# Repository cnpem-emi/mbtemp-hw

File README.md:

MBTemp
=====

MBTemp is an electronic board to acquire temperature in eight independent channels. It has been developed by the Control Group of Brazilian Synchrotron Light Laboratory (LNLS).

Example
-------

An example of use is present in the well documented file `exemplo-mbtemp.py`.

Contacts
-------------------------------------

Any doubts related to this projects, please do not hesitate to contact Robert Polli (robert.polli@cnpem.br)

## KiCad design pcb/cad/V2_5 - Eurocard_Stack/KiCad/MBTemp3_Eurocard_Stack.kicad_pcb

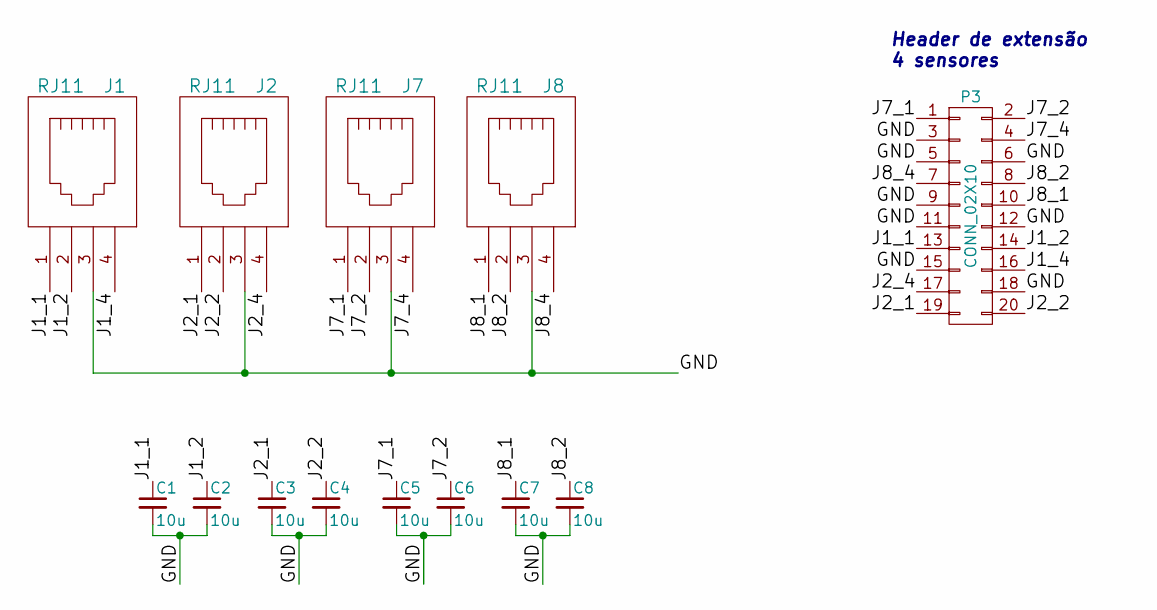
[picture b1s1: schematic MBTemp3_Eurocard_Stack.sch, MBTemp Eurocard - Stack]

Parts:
C1, C2, C3, C4, C5, C6, C7, C8: 10u; C_0805
J1, J2, J7, J8: RJ11
P3: CONN_02X10; Pin_Header_Straight_2x10

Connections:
/GND: C1.2, C2.2, C3.2, C4.2, C5.2, C6.2, C7.2, C8.2, J1.3, J2.3, J7.3, J8.3, P3.3, P3.5, P3.6, P3.9, P3.11, P3.12, P3.15, P3.18; also elsewhere on the board
/J1_1: C1.1, J1.1, P3.13
/J1_2: C2.1, J1.2, P3.14
/J1_4: J1.4, P3.16
/J2_1: C3.1, J2.1, P3.19
/J2_2: C4.1, J2.2, P3.20
/J2_4: J2.4, P3.17
/J7_1: C5.1, J7.1, P3.1
/J7_2: C6.1, J7.2, P3.2
/J7_4: J7.4, P3.4
/J8_1: C7.1, J8.1, P3.10
/J8_2: C8.1, J8.2, P3.8
/J8_4: J8.4, P3.7

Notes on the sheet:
Header de extensão 4 sensores

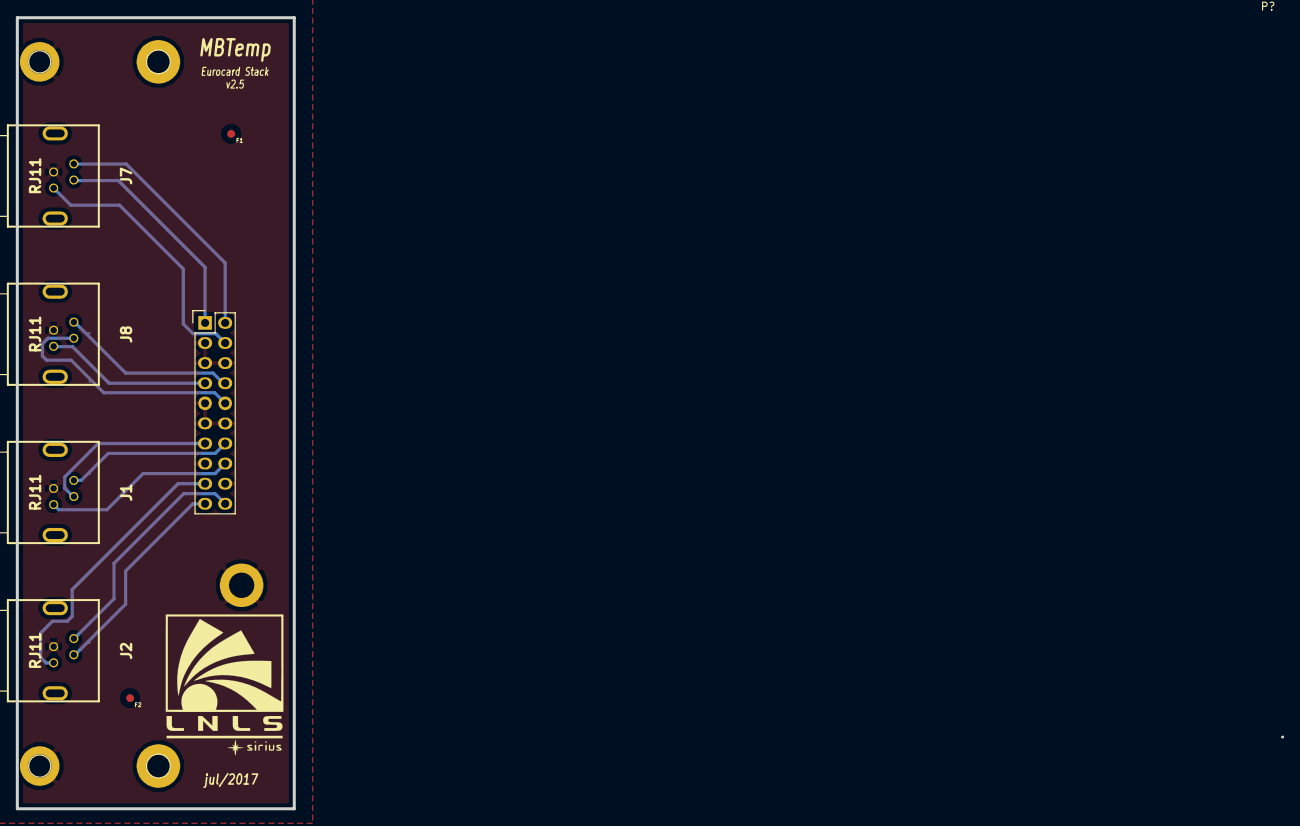
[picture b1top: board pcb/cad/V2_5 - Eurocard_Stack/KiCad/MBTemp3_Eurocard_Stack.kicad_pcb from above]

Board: 2 copper layers, 35.0 x 100.0 mm, 18 parts (0 on the bottom side), 13 nets.

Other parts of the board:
F1, F2, F3, F4: Fiducial_1mm_Dia_2.54mm_Outer_CopperBottom
P?: C64AC; Eurocard_template

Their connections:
/GND: P?.1, P?.2; also elsewhere on the board

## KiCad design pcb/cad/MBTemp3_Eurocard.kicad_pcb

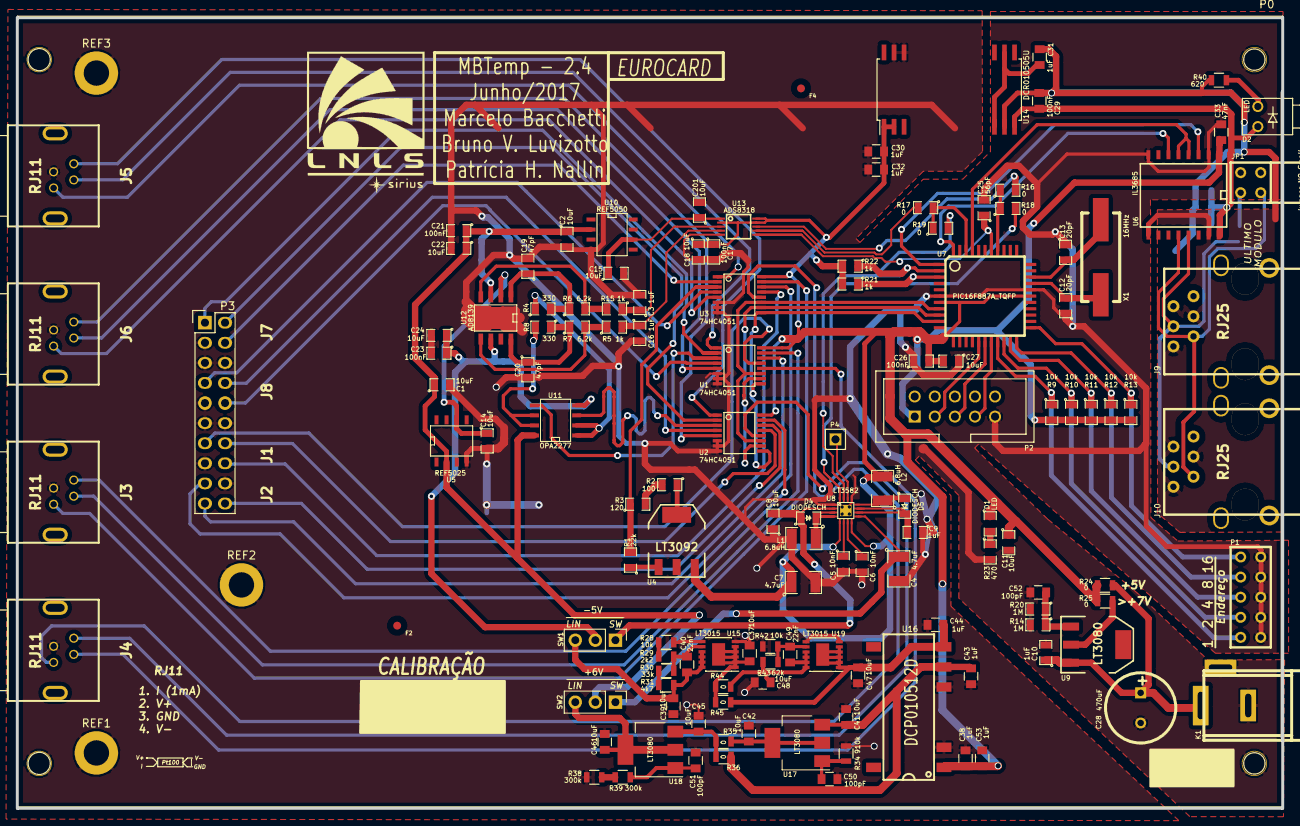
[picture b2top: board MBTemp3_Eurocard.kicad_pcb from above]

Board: 2 copper layers, 160.0 x 100.0 mm, 142 parts (0 on the bottom side), 101 nets.

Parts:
C1, C2, C8, C11, C14, C15, C18, C22, C24, C27, C201: 10uF; SM0805
C3, C9, C10, C16: 1uF; SM0805
C4, C7: 4.7uF; SM1210
C5, C6: 10nF; SM0805
C12, C13: 20pF; SM0805
C17, C21, C23, C26: 100nF; SM0805
C19, C20: 47pF; SM0805
C25: 56pF; SM0805
C28: 470uF; C1.5V8V
C29, C34: 100nF; C_0805
C30, C31, C32, C38, C43, C44, C53: 1uF; C_0805
C33, C35: 47nF; C_0805
C36: 10uF; TantalC_SizeR_EIA-2012
C37, C39, C41, C42, C45, C46, C47, C48: 10uF; C_0805
C40, C49: 22nF; C_0805
C50, C51, C52: 100pF; C_0805
D1: LED; SM0805
D2: LED; LED_para_painel_KINGBRIGHT
D4, D5: DIODESCH; SM0805
F1, F2, F3, F4: Fiducial; Fiducial_1mm_Dia_2.54mm_Outer_CopperBottom
J3, J4, J5, J6: RJ11; RJ11-4P4C-HIROSE
J9, J10: RJ25; Conector-6P6C_Erni-Amphenol-Stewart
JP1: Jumper_NO_Small; PIN_ARRAY_5x2
K1: Jack; J4_2.1mm
L1, L2: 6.8uH; SM1210
P0: EURO BOARD; Eurocard_template_(without_euro_connector)
P1: Endereço; PIN_ARRAY_5x2
P2: Programação; PIN_ARRAY_5x2
P3: CONN_02X10; Pin_Header_Straight_2x10
P4: CONN_1; PIN_ARRAY_1
R1: 22k; SM0805
R2: 100; SM0805
R3: 120; SM0805
R4, R8: 330; SM0805
R5, R15, R21, R22: 1k; SM0805
R6, R7: 6.2k; SM0805
R9, R10, R11, R12, R13: 10k; SM0805
R14, R20: 1M; SM0805
R16, R17, R18, R19: 0; SM0805
R23: 470; SM0805
R24, R25, R35, R36, R44, R45: 0; R_0805
R26: 120; R_0805
R28, R42: 10k; R_0805
R29: 2k2; R_0805
R30: 33k; R_0805
R31: 4k7; R_0805
R34: 910k; R_0805
R38, R39: 300k; R_0805
R40: 620; R_0805
R43: 62k; R_0805
REF1, REF2, REF3: M3; MountingHole_3.2mm_M3_ISO14580_Pad
SW1: -5V; Pin_Header_Straight_1x03_Pitch2.54mm
SW2: +6V; Pin_Header_Straight_1x03_Pitch2.54mm
U1, U2, U3: 74HC4051; SSOP16
U4: LT3092; SOT223
U5: REF5025; SO8E
U6: IL3685; SO16W
U7: PIC16F887A_TQFP; TQFP44
U8: LT3582; QFN16
U9: LT3080; SOT223
U10: REF5050; SO8E
U11: OPA2277; SO8E
U12: AD8139; SO8_WITH_EP
U13: ADS8318; MSOP10-0.5
U14: DCR010505U; DCR01XXXXU
U15, U19: LT3015; MSOP-12-1EP_3x4mm_Pitch0.65mm
U16: DCP010512D; DCP0105xxD
U17, U18: LT3080; SOT-223
X1: 16MHz; CrystalSMD

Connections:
+2,5V-REG: C14.1, U5.6, U12.2
+5V: C7.1, C11.1, C17.1, C18.1, C26.2, C27.2, C30.1, C32.1, C33.2, C38.1, C53.1, D1.1, L2.2, P2.1, R9.2, R10.2, R11.2, R12.2, R13.2, R21.2, R22.2, R24.2, R25.2, U1.16, U2.16, U3.16, U4.3, U6.1, U7.7, U7.28, U8.5, U8.8, U13.2, U13.9, U13.10, U14.1, U14.2, U16.1
+5V-REG: C15.1, C201.1, U10.6, U13.1
+5VP: C29.1, C34.2, C35.2, C36.1, D2.2, U6.16, U14.14
+6V: C1.1, C2.1, C21.1, C22.1, SW2.2, U5.2, U10.2, U11.8, U12.3
-5V: C23.1, C24.1, SW1.2, U11.4, U12.6
/Alimentacao/+6V_LIN: C46.1, SW2.3, U18.2
/Alimentacao/+6V_SW: C4.1, SW2.1, U8.9
/Alimentacao/+9.1V: C42.1, R35.2, U17.2
/Alimentacao/+12V: C41.1, C43.1, R36.1, U16.6, U17.3
/Alimentacao/-5V_LIN: C39.1, C40.2, R31.2, SW1.3, U15.9, U15.10, U15.11, U15.12
/Alimentacao/-5V_SW: C8.2, D4.1, SW1.1, U8.2
/Alimentacao/-8.5V_LIN: C48.1, C49.2, R43.2, R44.2, U19.9, U19.10, U19.11, U19.12
/Alimentacao/-12V: C44.1, C47.1, R45.2, U16.7, U19.1, U19.2, U19.3, U19.4, U19.5, U19.13
/Alimentacao/CAP: C9.2, D5.2, U8.10, U8.11
/Alimentacao/SWN: D4.2, L1.1, U8.3, U8.4
/Alimentacao/SWP: D5.1, L2.1, U8.12
/Alimentacao/VIN: C10.1, C28.1, K1.1, R24.1, U9.3
/J1_1: P3.13, U1.13
/J1_2: P3.14, U2.13
/J1_4: P3.16, U3.13
/J2_1: P3.19, U1.14
/J2_2: P3.20, U2.14
/J2_4: P3.17, U3.14
/J7_1: P3.1, U1.2
/J7_2: P3.2, U2.2
/J7_4: P3.4, U3.2
/J8_1: P3.10, U1.4
/J8_2: P3.8, U2.4
/J8_4: P3.7, U3.4
/PIC/A_485: J9.2, J10.2, JP1.1, U6.12
/PIC/B_485: J9.3, J10.3, R26.1, U6.13
/PIC/SCKpic: R16.1, R18.1, U7.37
/PIC/SDIpic: R17.1, R19.1, U7.42
A: U1.11, U2.11, U3.11, U7.8
AD-CONVST: C25.1, U7.38, U13.6
AD-IN+: C3.1, R5.1, U13.3
AD-IN-: C16.1, R15.2, U13.4
AD-SCLK: R16.2, U13.8
AD-SDO: R17.2, U13.7
B: U1.10, U2.10, U3.10, U7.9
C: U1.9, U2.9, U3.9, U7.10
GND: C1.2, C2.2, C3.2, C4.2, C5.2, C6.2, C7.2, C8.1, C9.1, C10.2, C11.2, C12.1, C13.1, C14.2, C15.2, C16.2, C17.2, C18.2, C19.2, C20.2, C21.2, C22.2, C23.2, C24.2, C25.2, C26.1, C27.1, C28.2, C30.2, C32.2, C33.1, C37.2, C38.2, C39.2, C41.2, C42.2, C43.2, C44.2, C45.2, C46.2, C47.2, C48.2, C50.2, C51.2, C52.2, C53.2, C201.2, J3.3, J4.3, J5.3, J6.3, K1.2, K1.3, L1.2, P0.1, P0.2, P1.1, P1.3, P1.5, P1.7, P1.9, P2.9, P3.3, P3.5, P3.6, P3.9, P3.11, P3.12, P3.15, P3.18, R14.2, R20.2, R23.2, R28.1, R34.2, R38.2, R42.1, REF1.1, REF2.1, REF3.1, U1.6, U1.7, U1.8, U2.6, U2.7, U2.8, U3.6, U3.7, U3.8, U5.4, U6.2, U6.8, U7.6, U7.29, U8.1, U8.13, U8.17, U10.4, U13.5, U14.26, U14.27, U15.6, U15.7, U16.2, U16.5, U19.6, U19.7
GNDREF: C29.2, C31.2, C34.1, C35.1, C36.2, J9.1, J9.4, J9.5, J10.1, J10.4, J10.5, R40.2, U6.9, U6.15, U14.13
LT-SCL: R18.2, R21.1, U7.3, U8.16
LT-SDA: R19.2, R22.1, U7.2, U8.15
unnamed: C5.1, U8.6
unnamed: C6.1, U8.7
unnamed: C12.2, U7.30, X1.2
unnamed: C13.2, U7.31, X1.1
unnamed: C19.1, R4.2, R6.1, U12.1
unnamed: C20.1, R7.1, R8.1, U12.8
unnamed: C31.1, U14.12, U14.16
unnamed: C37.1, R44.1, R45.1, U15.1, U15.2, U15.3, U15.4, U15.5, U15.13
unnamed: C40.1, R29.2, R30.1, U15.8
unnamed: C45.1, R35.1, R36.2, U18.3
unnamed: C49.1, R42.2, R43.1, U19.8
unnamed: C50.1, R34.1, U17.1
unnamed: C51.1, R39.1, U18.1
unnamed: C52.1, R14.1, R20.1, U9.1
unnamed: D1.2, R23.1
unnamed: D2.1, R40.1
unnamed: J3.1, U1.15
unnamed: J3.2, U2.15
unnamed: J3.4, U3.15
unnamed: J4.1, U1.12
unnamed: J4.2, U2.12
unnamed: J4.4, U3.12
unnamed: J5.1, U1.1
unnamed: J5.2, U2.1
unnamed: J5.4, U3.1
unnamed: J6.1, U1.5
unnamed: J6.2, U2.5
unnamed: J6.4, U3.5
unnamed: JP1.2, R26.2
unnamed: P1.2, R9.1, U7.19
unnamed: P1.4, R10.1, U7.20
unnamed: P1.6, R11.1, U7.21
unnamed: P1.8, R12.1, U7.22
unnamed: P1.10, R13.1, U7.23
unnamed: P2.3, U7.16
unnamed: P2.5, U7.17
unnamed: P2.7, U7.18
unnamed: R1.1, U4.1
unnamed: R1.2, R3.1, U3.3
unnamed: R2.1, U4.4
unnamed: R2.2, R3.2
unnamed: R4.1, U11.1, U11.2
unnamed: R5.2, R6.2, U12.4
unnamed: R8.2, U11.6, U11.7
unnamed: R7.2, R15.1, U12.5
unnamed: R25.1, U9.2
unnamed: R28.2, R29.1
unnamed: R30.2, R31.1
unnamed: R38.1, R39.2
unnamed: U6.3, U7.1
unnamed: U6.4, U6.5, U7.41
unnamed: U6.6, U7.44
PT100_Diff+: U1.3, U11.5
PT100_Diff-: U2.3, U11.3
VPP: P4.1, U8.14

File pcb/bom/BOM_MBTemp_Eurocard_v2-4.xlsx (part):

MUDANÇAS | Designator | Description | Value | Part Number | Package | Manufacturer | Quantity | Qtty 300 placas | COMPRAR | PN CNPEM | Item na SC? | Obs | Preco unitário | Total | Total efetivo
 | C13,C12 | Ceramic Capacito 20pF 50V 5% SMD 0805 NP0 | 20pF | CL21C200JBANNNC | 0805 | Samsung ElectroMechanics | 2 | 600 | 4000 | MT104425 | 1 | ROLO | 0.02 | 0.04 | 47.84
 | C20,C19 | Ceramic Capacitor 47pF 50V 5% SMD 0805 NP0 | 47pF | CL21C470JBANNNC | 0805 | Samsung ElectroMechanics | 2 | 600 | 4000 | MT104426 | 1 | ROLO | 0.02 | 0.04 | 38.64
 | C25 | Ceramic Capacitor 56pF 50V 5% SMD 0805 NP0 | 56pF | CL21C560JBANNNC | 0805 | Samsung ElectroMechanics | 1 | 300 | 0 (Temos rolo) | MT104427 | 0 | ROLO | 0.02 | 0.02 | 0
 | C26,C23,C21,C17,C29,C34 | Multilayer Ceramic Capacitor 100nF 50V ±5% SMD 0805 X7R | 100nF | 08055C104JAT2A | 0805 | AVX | 6 | 1800 | 4000 | MT104382 | 1 | ROLO | 0.1 | 0.6 | 48.32
 | C27,C24,C22,C18,C2,C15,C14,C1,C8,C11,C201,C37,C39,C47,C48,C41,C42,C45,C46 | Ceramic Capacitor 10uF 16V ±10% SMD 0805 X5R | 10uF | CL21A106KOQNNNE | 0805 | Samsung ElectroMechanics | 19 | 5700 | 8000 | MT104058 | 1 | ROLO | 0.06 | 1.14 | 304.92
 | C28 | Aluminium Radial Capacitor 470uF 16V 20% PTH | 470uF | ECA-1CM471 | Radial Can | Panasonic Electronic Components | 1 | 300 | 500 | MT104059 | 1 |  | 0.11 | 0.11 | 49.27
 | C30,C31,C32,C3,C16,C10,C9,C38,C43,C44,C53 | Ceramic Capacitor 1uF 16V ±5% SMD 0805 X7R | 1u | C0805C105J4RACTU | 0805 | Kemet | 11 | 3300 | 4000 | MT104060 | 1 | ROLO | 0.1 | 1.1 | 246.31
 | C33,C35 | Multilayer Ceramic Capacitor 47nF 100V 5% SMD 0805 X7R | 47nF | 08051C473JAT2A | 0805 | AVX | 2 | 600 | 2000 | MT104243 | 1 | ROLO | 0.11 | 0.22 | 138.6
 | C36 | Tantalum Capacitor 10uF, 10V, 10%, ESR 3.8ohm | 10uF | T491A106K010AT7280 | 1206 | Kemet | 1 | 300 | 500 | AP111595 | 1 |  | 0.13 | 0.13 | 61.84
TROCADO PARA 1uF |  | Ceramic Capacitor 470nF 25V ±5% SMD 0805 X7R | 470n | CL21B474JAFNNNE | 0805 | Samsung ElectroMechanics | 0 | 0 | 2000 | MT104061 | 1 | ROLO | 0.07 | 0 | 104.92
 | C4,C7 | Ceramic Capacitor 4.7uF 50V 10% SMD 1210 X7R | 4.7uF | GRM32ER71H475KA88L | 1210 | Murata | 2 | 600 | 1000 | MT104428 | 1 | ROLO | 0.31 | 0.62 | 196.35
 | C40,C49 | Ceramic Capacitor 22nF 100V 5% SMD 0805 X7R | 22n | 08051C223JAT2A | 0805 | Murata | 2 | 600 | 0 (Temos rolo) | MT104429 | 0 | ROLO | 0.1 | 0.2 | 0
 | C50,C51,C52 | Ceramic Capacitor 100pF 50V 5% SMD 0805 NP0 | 100pF | C0805C101J5GACTU | 0805 | Kemet | 3 | 900 | 4000 | MT104242 | 1 | ROLO | 0.1 | 0.3 | 36.72
 | C6,C5 | Ceramic Capacitor 10nF 50V 5% SMD 0805 C0G | 10nF | GRM2195C1H103JA01D | 0805 | Murata | 2 | 600 | 4000 | AP111901 | 1 | ROLO | 0.11 | 0.22 | 292.16
 | D1 | Green LED, 2.1V, 20mA, SMD 0805 | LED Green | LTST-C171GKT | 0805 | Lite-On Inc | 1 | 300 | 0 (Temos rolo) | AP111654 |  | ROLO | 0.08 | 0.08 | 0
 | D2 | LED Circuit Board Indicator Single Red Diffused, Through Hole, Right Angle | LED Red | WP934CB/ID | 2x1 PTH pitch 2,54mm | Kingbright | 1 | 300 | 390 | AP110389 | 1 |  | 0.21 | 0.21 | 82.134
 | D4,D5 | Diodo Schottky 20V 500mA DC SMD 0805 | Diode Sch | SD0805S020S0R5 | 0805 | AVX Corporation | 2 | 600 | 1000 | AP103285 | 1 |  | 0.18 | 0.36 | 114.64
 | J4,J3,J6,J5 | RJ11 Jack connector Right Angle | RJ11 | TM5RJ3-44(50) | 4P4C | Hirose Electric Co | 4 | 1200 | 1560 | AP110402 | 1 |  | 1.73 | 6.92 | 1987.44
 | J9,J10 | RJ25 | RJ25 | 133623 | 6P6C | ERNI | 2 | 600 | 780 | AP109847 |  |  | 1 | 2 | 390
 | JP1 | Dip Switch SPST 2 Position Through Hole, Right Angle Slide (Standard) Actuator 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 | DIP switch 2pos Right Angle | KAS2102E | DIP Switch Right Angle PTH | E-Switch | 1 | 300 | 390 | AP110400 | 1 |  | 0.999 | 0.999 | 389.766
 | K1 | Power Barrel Jack Connector 2mm ID, 5.5mm OD, PTH, right angle | Jack | PJ-002AH | Jack J4-5.5mm 2.0mm | CUI Inc | 1 | 300 | 390 | MT104062 | 1 |  | 0.49 | 0.49 | 190.008
 | L2,L1 | 6.8uH shielded wirewound Inductor 850mA 288mOhm | 6.8uH | LQH32PN6R8NN0L | 1210 | Murata | 2 | 600 | 0 (Temos rolo) |  | 0 | ROLO | 0.22 | 0.44 | 0
 | P1 | DIP Switch slide 5 positions SPST right angle PTH | DIP Switch slide SPST right angle PTH | KAS2105E | PIN_ARRAY_5x2 | E-Switch | 1 | 300 | 390 | MT103732 | 1 |  | 1.2 | 1.2 | 467.5788
 | P2 | 10 positions Male Header, PTH, Shrouded Connector, Pitch 2.54mm | Header 2x05 | 302-S101 | Straight_2x05 Shrouded pitch 2.54mm | On Shore Technology Inc | 1 | 300 | 390 | AP103279 | 1 |  | 0.17 | 0.17 | 64.35
 | P3 | Conector 2x10 pitch 2.54mm | CONN_02X10 | DW-10-09-F-D-425 | Pin_Header_Straight_2x10 | Samtec | 1 | 300 | 390 | MT104063 |  |  | 1 | 1 | 390
 | R1 | Resistor 22K ohm 0,1% 1/8W SMD 0805 Thin Film | 22kΩ | ERA-6AEB223V | 0805 | Panasonic Electronic Components | 1 | 300 | 5000 | MT104109 | 1 | ROLO | 0.09 | 0.09 | 187.43
 | R17,R16,R24,R36,R45 | Resistor Jumper 0 ohm 1% 1/8W SMD 0805 Thick Film | 0Ω | RC0805JR-070RL | 0805 | Yageo | 5 | 1500 | 5000 | MT100803 | 1 | ROLO | 0.01 | 0.05 | 10.55
 | R19,R18,R25,R35,R44 | Resistor Jumper 0 ohm 1% 1/8W SMD 0805 Thick Film | 0 | RC0805JR-070RL | 0805 | Yageo | 5 | ---- | --- | ---- | 0 | NAO MONTAR!
 | R2 | Resistor 100 ohm 0,1% 1/8W SMD 0805 Thin Film | 100Ω | ERA-6AEB101V | 0805 | Panasonic Electronic Components | 1 | 300 | 5000 | MT104084 | 1 | ROLO | 0.09 | 0.09 | 187.43
 | R20,R14 | Resistor 1 Mohm 1% 1/8W SMD 0805 Thick Film | 1MΩ | RC0805FR-071ML | 0805 | Yageo | 2 | 600 | 5000 | MT104430 | 1 | ROLO | 0.09 | 0.18 | 13.59
 | R15,R5 | Resistor 1K ohm 0,1% 1/8W SMD 0805 Thin Film | 1kΩ | ERA-6AEB102V | 0805 | Panasonic Electronic Components | 2 | 600 | 5000 | MT104085 | 1 | ROLO | 0.09 | 0.18 | 187.45
 | R21,R22 | Resistor 1K ohm 1% 1/8W SMD 0805 Thick Film | 1kΩ | RC0805FR-071KL | 0805 | Yageo | 2 | 600 | 5000 | MT104228 | 1 | ROLO | 0.01 | 0.02 | 15
 | R23 | Resistor 470 ohm 1% 1/8W SMD 0805 Thick Film | 470Ω | RC0805FR-07470RL | 0805 | Yageo | 1 | 300 | 5000 | MT104431 | 1 | ROLO | 0.01 | 0.01 | 15
 | R40 | Resistor 620 ohm 1% 1/8W SMD 0805 Thick Film | 620Ω | RC0805FR-07620RL | 0805 | Yageo | 1 | 300 | 5000 | MT104227 | 1 | ROLO | 0.01 | 0.01 | 15
 | R29 | Resistor 2.2 k ohm 1% 1/8W SMD 0805 Thick Film | 2.2kΩ | RC0805FR-072K2L | 0805 | Yageo | 1 | 300 | 5000 | MT104237 | 1 | ROLO | 0.01 | 0.01 | 15
 | R3 | Resistor 120 ohm 0,1% 1/8W SMD 0805 Thin Film | 120Ω | ERA-6AEB121V | 0805 | Panasonic Electronic Components | 1 | 300 | 5000 | MT104086 | 1 | ROLO | 0.09 | 0.09 | 187.45
NOVO PN | R26 | Resistor 120 ohm 1% 0.4W SMD 0805 Thick Film | 120Ω | ESR10EZPF1200 | 0805 | Rohm Semiconductor | 1 | 300 | 5000 | MT104449 | 0 | ROLO/SC SERIAL | 0.01 | 0.01 | 125
 | R30 | Resistor 33 k ohm 1% 1/8W SMD 0805 Thick Film | 33kΩ | RC0805FR-0733KL | 0805 | Yageo | 1 | 300 | 5000 | MT104432 | 1 | ROLO | 0.01 | 0.01 | 15
 | R31 | Resistor 4.7 k ohm 1% 1/8W SMD 0805 Thick Film | 4.7kΩ | RC0805FR-074K7L | 0805 | Yageo | 1 | 300 | 5000 | MT104433 | 1 | ROLO | 0.01 | 0.01 | 15
 | R34 | Resistor 910 k ohm 1% 1/8W SMD 0805 Thick Film | 910kΩ | RC0805FR-07910KL | 0805 | Yageo | 1 | 300 | 5000 | MT104231 | 1 | ROLO | 0.01 | 0.01 | 15
 | R38, R39 | Resistor 300k ohm ±0,1% 1/8W SMD 0805 Thin Film | 300kΩ | RT0805BRD07300KL | 0805 | Yageo | 1 | 300 | 5000 | MT104087 | 1 | ROLO | 0.01 | 0.01 | 187.45
 | R43 | Resistor 62 k ohm 1% 1/8W SMD 0805 Thick Film | 62kΩ | RC0805FR-0762KL | 0805 | Yageo | 1 | 300 | 5000 | MT104434 | 1 | ROLO | 0.01 | 0.01 | 15
 | R6,R7 | Resistor 6.2 k ohm 0,1% 1/8W SMD 0805 Thin Film | 6.2kΩ | ERA-6AEB622V | 0805 | Panasonic Electronic Components | 2 | 600 | 5000 | MT104088 | 1 | ROLO | 0.09 | 0.18 | 187.45
 | R8,R4 | Resistor 330 ohm, 0,1%, 1/8W, SMD 0805, Thin Film | 330Ω | ERA-6AEB331V | 0805 | Panasonic Electronic Components | 2 | 600 | 5000 | MT104089 | 1 | ROLO | 0.09 | 0.18 | 187.45
 | R9,R10,R11,R12,R13,R28,R42 | Resistor 10K ohm 1% 1/8W SMD 0805 Thick Film | 10kΩ | RC0805FR-0710KL | 0805 | Yageo | 7 | 2100 | 5000 | MT104235 | 1 | ROLO | 0.01 | 0.07 | 15
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
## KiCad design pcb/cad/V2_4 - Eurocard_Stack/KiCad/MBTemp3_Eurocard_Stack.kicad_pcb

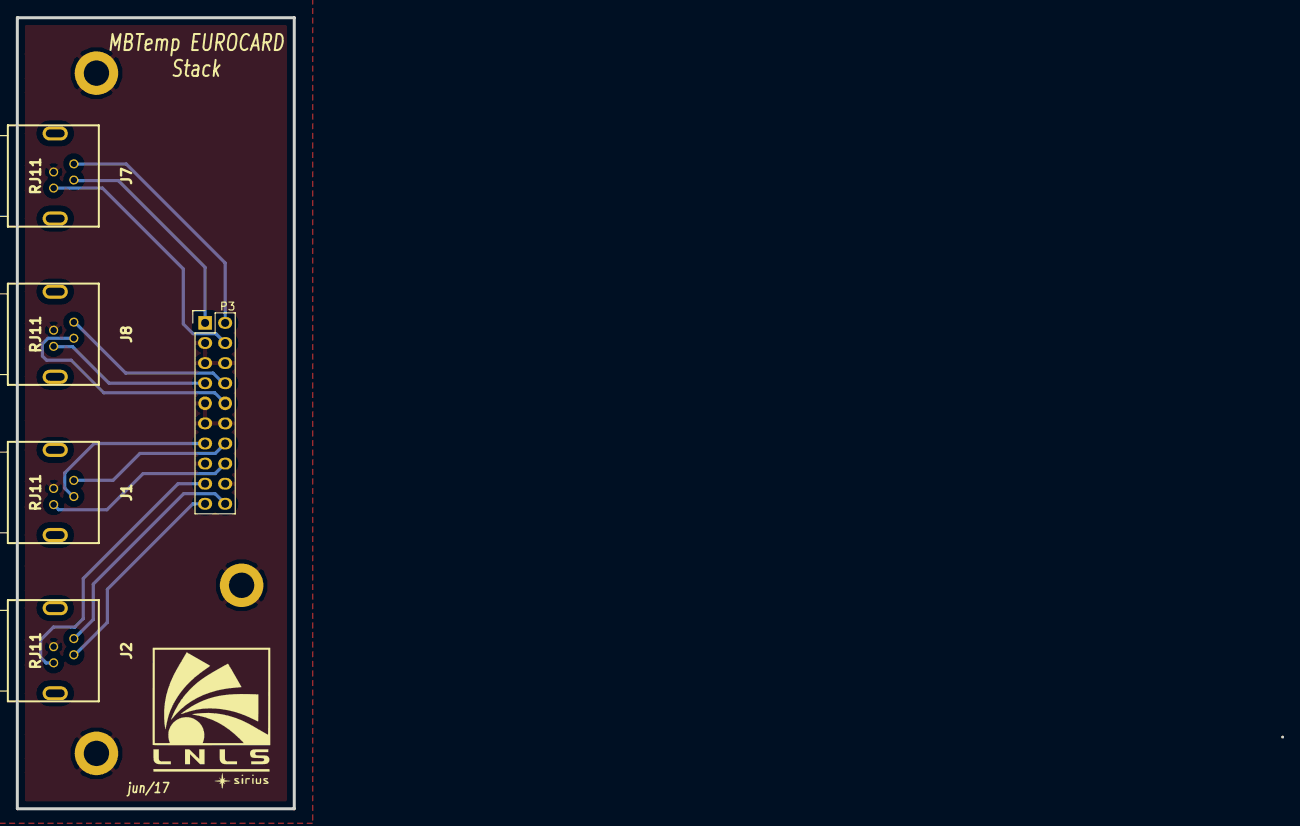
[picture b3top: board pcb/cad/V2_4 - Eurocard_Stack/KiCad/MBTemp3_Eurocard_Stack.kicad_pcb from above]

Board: 2 copper layers, 35.0 x 100.0 mm, 5 parts (0 on the bottom side), 13 nets.

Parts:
J1, J2, J7, J8: RJ11; RJ11-4P4C-HIROSE
P3: MBTemp_Stack; Pin_Header_Straight_2x10

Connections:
/GND: J1.3, J2.3, J7.3, J8.3, P3.3, P3.5, P3.6, P3.9, P3.11, P3.12, P3.15, P3.18
/J1_1: J1.1, P3.13
/J1_2: J1.2, P3.14
/J1_4: J1.4, P3.16
/J2_1: J2.1, P3.19
/J2_2: J2.2, P3.20
/J2_4: J2.4, P3.17
/J7_1: J7.1, P3.1
/J7_2: J7.2, P3.2
/J7_4: J7.4, P3.4
/J8_1: J8.1, P3.10
/J8_2: J8.2, P3.8
/J8_4: J8.4, P3.7

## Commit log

2023-12-20 v2.3
2023-12-20 v2.4
2023-12-20 v2.5
2023-12-20 v2.6
